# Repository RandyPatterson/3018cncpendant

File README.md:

# Pendant Controller for 3018 CNC
An Arduino based Handwheel Pendant for a generic 3018 CNC.  Allows you to easily move the X, Y and Z axis using the handwheel.  You can dial in the exact position using the 0.1 mm/step or quickly move to a new location using the 1.0 mm/step buttons.

### Required Hardware
1. 1x Arduino Pro Mini (or compatible)
1. 1x KY-040 Rotary Encoder ([Amazon](https://www.amazon.com/gp/product/B07D356LRH/ref=ppx_yo_dt_b_asin_title_o04_s00?ie=UTF8&psc=1))
1. 1x SP3T Rotary Switch ([Amazon](https://www.amazon.com/gp/product/B018LYU3OO/ref=ppx_yo_dt_b_asin_title_o01_s00?ie=UTF8&psc=1))
1. 4x M3 x 6mm screws
1. 4x M3 x 5mm x 3mm thread inserts ([Amazon](https://www.amazon.com/cSeao-120pcs-Inserted-Knurled-Embedded/dp/B07D683Q26/ref=sr_1_4?crid=11IEQW4CEOOYW&keywords=m3%2B5mm%2Bthread%2Binserts&qid=1643132299&sprefix=m3%2B5mm%2Bthread%2Binserts%2Caps%2C78&sr=8-4&th=1]))
1. 2x 12mm momentary SPST square push buttons
1. 1x 2x4 (8 pin) 2.54mm pitch flat ribbon cable
1. 1x 2x4 2.54mm pitch connector (optional, for PCB) ([Amazon](https://www.amazon.com/gp/product/B07WPBQPBT/ref=ppx_yo_dt_b_asin_title_o03_s00?ie=UTF8&psc=1))

### This repo includes
1. [/src](/src) = Source code for an Arduino Pro Mini (PlatformIO)
1. [/pcb](/pcb) = Schematic and PCB layout (KiCad)
1. [/model](/model) = STEP, Fusion360 and 3MF files for 3D printing the case and handwheel

## Source Code
Build using the PlatformIO plugin for VS Code.  Targeting Arduino Pro Mini but any board can be used as long as it has at least 7 open IO Ports

## Schematic (Optional) 
Optional schematic and PCB to help cleanup the wiring.  Bypass capacitors are used on the encoder data lines to help reduce switch bounce.

### PCB

## Models
3D Models for case and handwheel to 3D print.  I used a resin printer but the models should be easily printable on FDM Printers.  The Models directory includes the SMF files to print unmodified and STEP files included for situations where you want to modify the 3D models in your favorite CAD program.  Fusion 360 files also included.

### Case & Handwheel Models

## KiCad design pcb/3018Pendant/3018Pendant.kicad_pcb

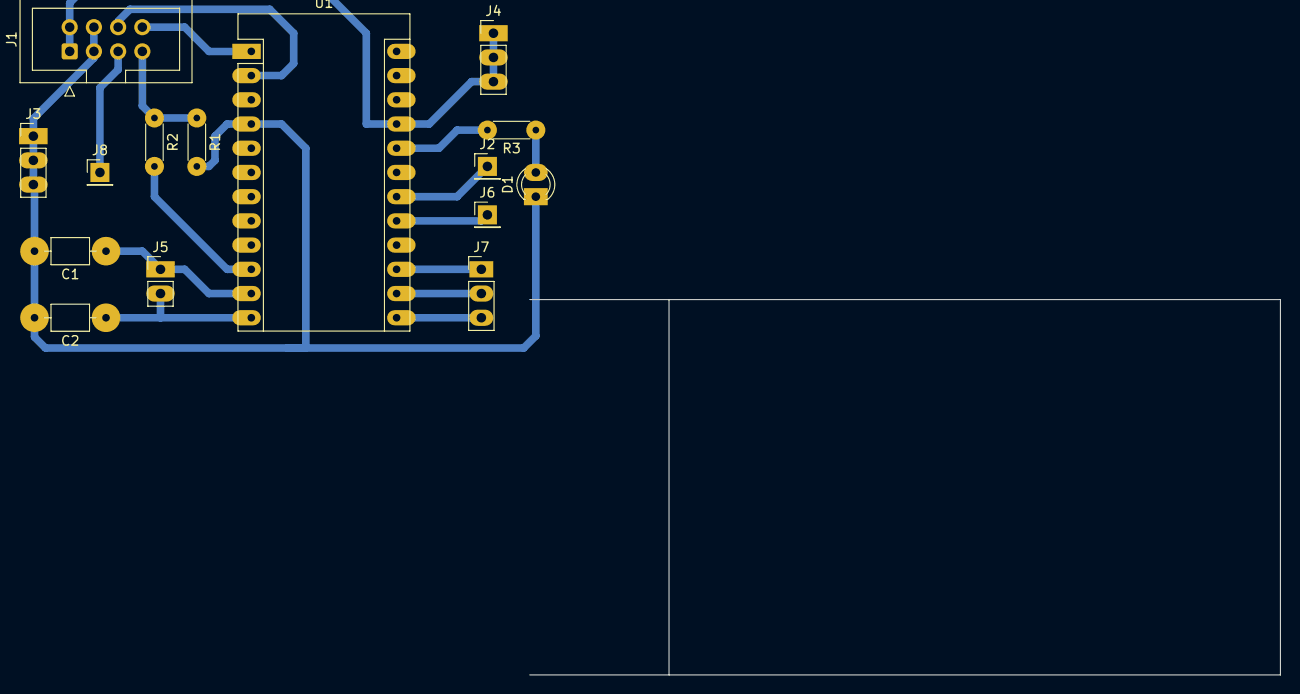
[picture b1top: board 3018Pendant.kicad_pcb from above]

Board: 2 copper layers, 78.7 x 39.4 mm, 15 parts (0 on the bottom side), 16 nets.

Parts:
C1, C2: .1 uF; C_Axial_L3.8mm_D2.6mm_P7.50mm_Horizontal
D1: LED; LED_D3.0mm_Clear
J1: Conn_02x04_Odd_Even; IDC-Header_2x04_P2.54mm_Vertical
J2: SW 1; PinHeader_1x01_P2.54mm_Vertical
J3: GND; PinHeader_1x03_P2.54mm_Vertical
J4: Vcc; PinHeader_1x03_P2.54mm_Vertical
J5: Encoder 1; PinHeader_1x02_P2.54mm_Vertical
J6: SW 2; PinHeader_1x01_P2.54mm_Vertical
J7: SW XYZ; PinHeader_1x03_P2.54mm_Vertical
J8: SW RESET; PinHeader_1x01_P2.54mm_Vertical
R1, R2, R3: 1K; R_Axial_DIN0204_L3.6mm_D1.6mm_P5.08mm_Horizontal
U1: Arduino_Pro_Mini; Arduino_Pro_Mini_copy

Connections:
GND: C1.2, C2.2, D1.1, J1.3, J1.4, J3.1, J3.2, J3.3, R1.2, U1.4, U1.23
unnamed: C1.1, J5.1, U1.11
unnamed: C2.1, J5.2, U1.12
unnamed: D1.2, R3.1
unnamed: J1.5, J8.1
unnamed: J1.6, U1.2
unnamed: J1.7, R1.1, R2.1
unnamed: J1.8, U1.1
unnamed: J2.1, U1.18
unnamed: J6.1, U1.17
unnamed: J7.1, U1.15
unnamed: J7.2, U1.14
unnamed: J7.3, U1.13
unnamed: R2.2, U1.10
unnamed: R3.2, U1.20
Vcc: J1.1, J1.2, J4.1, J4.2, J4.3, U1.21

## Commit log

2022-01-20 added XYZ to code
2022-01-24 initial state
2022-01-25 fix link type in readme
2022-01-25 type
2022-01-26 update to files
2022-01-27 add code to detect USB Device connected
2022-01-27 Update schematic & PCB to include reset button
2022-01-27 update images
2022-01-27 Add LED
2022-02-21 final version
2022-02-21 update docs
2023-01-04 minor docs update
